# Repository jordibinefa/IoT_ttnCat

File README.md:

# IoT_ttnCat
IoT board designed to be used on ttn.cat workshops

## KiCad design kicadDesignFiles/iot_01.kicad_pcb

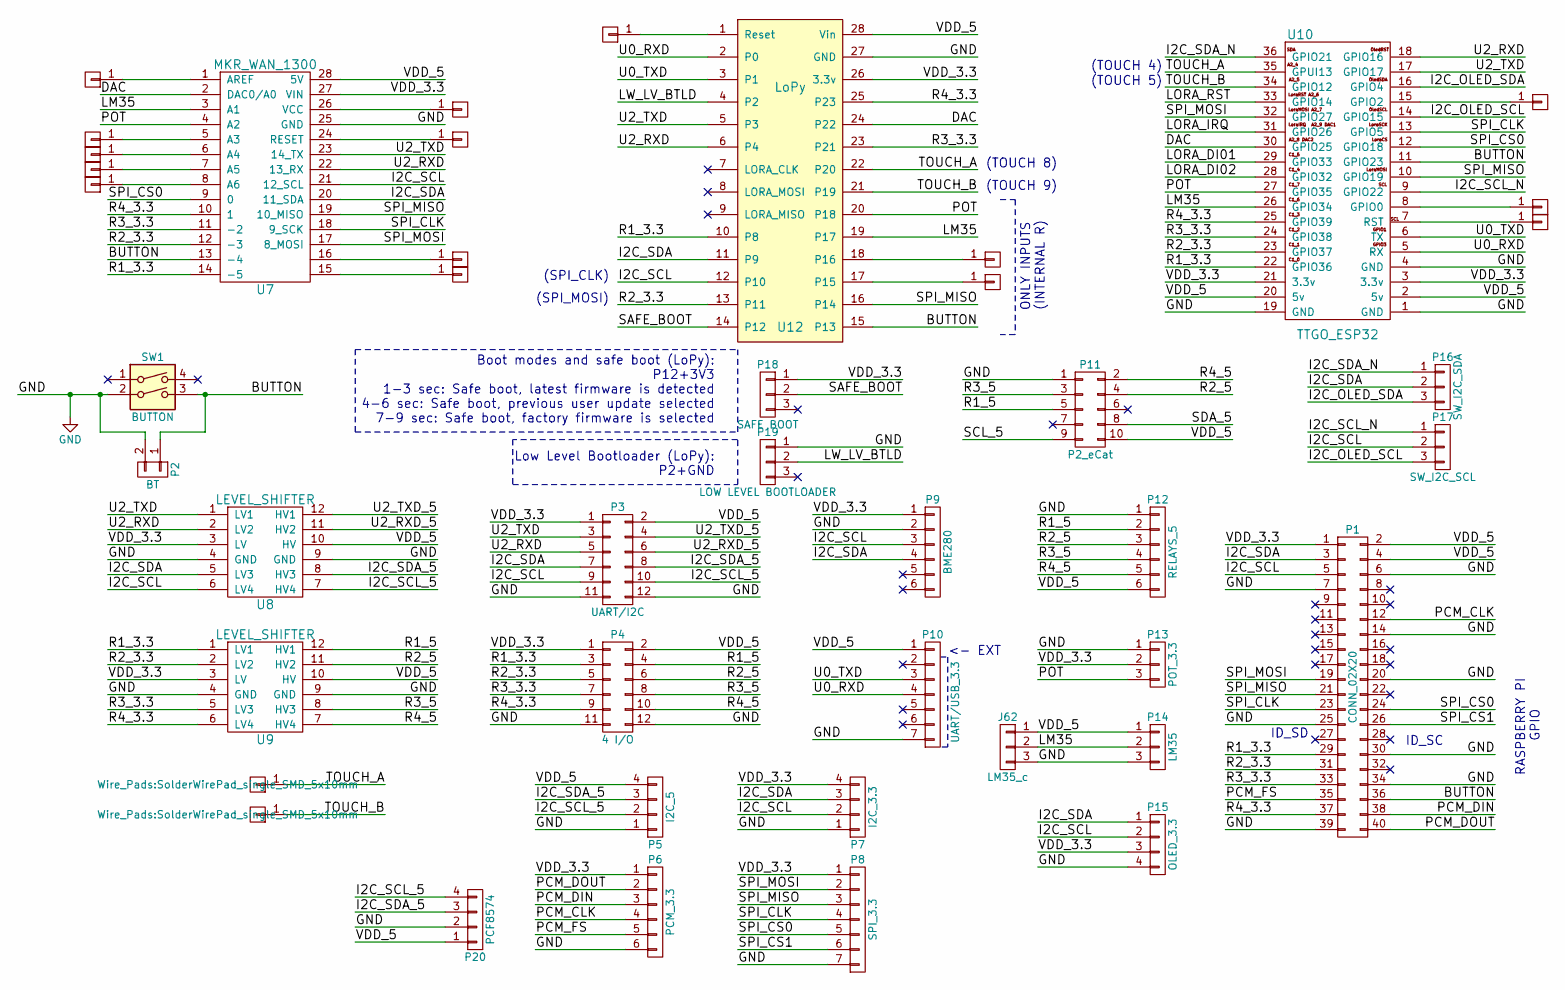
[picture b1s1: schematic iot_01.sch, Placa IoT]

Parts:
J1, J2: Conn_01x01; SolderWirePad_single_SMD_5x10mm
J39, J40, J41, J42, J43, J45, J46, J47, J48, J49, J60, J61, J70, J71, J72: Conn_01x01; Measurement_Point_Square-TH_Small
J62: LM35_c; TO-92_Inline_Wide
P1: CONN_02X20; IDC_Header_Straight_40pins
P2: BT; Pin_Header_Straight_1x02
P3: UART/I2C; Pin_Header_Straight_2x06
P4: 4 I/O; Pin_Header_Straight_2x06
P5: I2C_5; Pin_Header_Straight_1x04
P6: PCM_3.3; Pin_Header_Straight_1x06
P7: I2C_3.3; Pin_Header_Straight_1x04
P8: SPI_3.3; Pin_Header_Straight_1x07
P9: BME280; Pin_Header_Straight_1x06
P10: UART/USB_3.3; Pin_Header_Angled_1x07
P11: P2_eCat; CONN_5_eCAT
P12: RELAYS_5; Pin_Header_Angled_1x06
P13: POT_3.3; Pin_Header_Angled_1x03
P14: LM35; Pin_Header_Straight_1x03
P15: OLED_3.3; Pin_Header_Straight_1x04
P16: SW_I2C_SDA; Pin_Header_Straight_1x03
P17: SW_I2C_SCL; Pin_Header_Straight_1x03
P18: SAFE BOOT; Pin_Header_Straight_1x03
P19: LOW LEVEL BOOTLOADER; Pin_Header_Straight_1x03
P20: PCF8574; Pin_Header_Angled_1x04
SW1: BUTTON; BUTTON_THROUGH_HOLE
U7: MKR_WAN_1300
U8, U9: LEVEL_SHIFTER
U10: TTGO_ESP32
U12: LoPy; LoPy_with_headers

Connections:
/BUTTON: P1.36, P2.1, SW1.3, U7.13 (-4), U10.11 (GPIO23), U12.15 (P13)
/DAC: U7.2 (DAC0/A0), U10.30 (GPIO25), U12.24 (P22)
/I2C_OLED_SCL: P17.3, U10.14 (GPIO15)
/I2C_OLED_SDA: P16.3, U10.16 (GPIO4)
/I2C_SCL: P1.5, P3.9, P7.2, P9.3, P15.2, P17.2, U7.21 (12_SCL), U8.6 (LV4), U12.12 (P10)
/I2C_SCL_5: P3.10, P5.2, P20.4, U8.7 (HV4)
/I2C_SCL_N: P17.1, U10.9 (GPIO22)
/I2C_SDA: P1.3, P3.7, P7.3, P9.4, P15.1, P16.2, U7.20 (11_SDA), U8.5 (LV3), U12.11 (P9)
/I2C_SDA_5: P3.8, P5.3, P20.3, U8.8 (HV3)
/I2C_SDA_N: P16.1, U10.36 (GPIO21)
/LM35: J62.2, P14.2, U7.3 (A1), U10.26 (GPIO34), U12.19 (P17)
/LORA_DI01: U10.29 (GPIO33)
/LORA_DI02: U10.28 (GPIO32)
/LORA_IRQ: U10.31 (GPIO26)
/LORA_RST: U10.33 (GPIO14)
/LW_LV_BTLD: P19.2, U12.4 (P2)
/PCM_CLK: P1.12, P6.4
/PCM_DIN: P1.38, P6.3
/PCM_DOUT: P1.40, P6.2
/PCM_FS: P1.35, P6.5
/POT: P13.3, U7.4 (A2), U10.27 (GPIO35), U12.20 (P18)
/R1_3.3: P1.29, P4.3, U7.14 (-5), U9.1 (LV1), U10.22 (GPIO36), U12.10 (P8)
/R1_5: P4.4, P11.5, P12.2, U9.12 (HV1)
/R2_3.3: P1.31, P4.5, U7.12 (-3), U9.2 (LV2), U10.23 (GPIO37), U12.13 (P11)
/R2_5: P4.6, P11.4, P12.3, U9.11 (HV2)
/R3_3.3: P1.33, P4.7, U7.11 (-2), U9.5 (LV3), U10.24 (GPIO38), U12.23 (P21)
/R3_5: P4.8, P11.3, P12.4, U9.8 (HV3)
/R4_3.3: P1.37, P4.9, U7.10 (1), U9.6 (LV4), U10.25 (GPIO39), U12.25 (P23)
/R4_5: P4.10, P11.2, P12.5, U9.7 (HV4)
/SAFE_BOOT: P18.2, U12.14 (P12)
/SCL_5: P11.9
/SDA_5: P11.8
/SPI_CLK: P1.23, P8.4, U7.18 (9_SCK), U10.13 (GPIO5)
/SPI_CS0: P1.24, P8.5, U7.9 (0), U10.12 (GPIO18)
/SPI_CS1: P1.26, P8.6
/SPI_MISO: P1.21, P8.3, U7.19 (10_MISO), U10.10 (GPIO19), U12.16 (P14)
/SPI_MOSI: P1.19, P8.2, U7.17 (8_MOSI), U10.32 (GPIO27)
/TOUCH_A: J1.1, U10.35 (GPUI13), U12.22 (P20)
/TOUCH_B: J2.1, U10.34 (GPIO12), U12.21 (P19)
/U0_RXD: P10.4, U10.5 (RX), U12.2 (P0)
/U0_TXD: P10.3, U10.6 (TX), U12.3 (P1)
/U2_RXD: P3.5, U7.22 (13_RX), U8.2 (LV2), U10.18 (GPIO16), U12.6 (P4)
/U2_RXD_5: P3.6, U8.11 (HV2)
/U2_TXD: P3.3, U7.23 (14_TX), U8.1 (LV1), U10.17 (GPIO17), U12.5 (P3)
/U2_TXD_5: P3.4, U8.12 (HV1)
/VDD_3.3: P1.1, P3.1, P4.1, P6.1, P7.4, P8.1, P9.1, P13.2, P15.3, P18.1, U7.27 (VIN), U8.3 (LV), U9.3 (LV), U10.3 (3.3v), U10.21 (3.3v), U12.26 (3.3v)
/VDD_5: J62.1, P1.2, P1.4, P3.2, P4.2, P5.4, P10.1, P11.10, P12.6, P14.1, P20.1, U7.28 (5V), U8.10 (HV), U9.10 (HV), U10.2 (5v), U10.20 (5v), U12.28 (Vin)
GND: J62.3, P1.6, P1.7, P1.14, P1.20, P1.25, P1.30, P1.34, P1.39, P2.2, P3.11, P3.12, P4.11, P4.12, P5.1, P6.6, P7.1, P8.7, P9.2, P10.7, P11.1, P12.1, P13.1, P14.3, P15.4, P19.1, P20.2, SW1.2, U7.25 (GND), U8.4 (GND), U8.9 (GND), U9.4 (GND), U9.9 (GND), U10.1 (GND), U10.4 (GND), U10.19 (GND), U12.27 (GND)
unnamed: J39.1, U7.1 (AREF)
unnamed: J40.1, U7.5 (A3)
unnamed: J41.1, U7.6 (A4)
unnamed: J42.1, U7.7 (A5)
unnamed: J43.1, U7.8 (A6)
unnamed: J45.1, U7.26 (VCC)
unnamed: J46.1, U7.24 (RESET)
unnamed: J47.1, U7.16
unnamed: J48.1, U7.15
unnamed: J49.1, U12.1 (Reset)
unnamed: J60.1, U12.18 (P16)
unnamed: J61.1, U12.17 (P15)
unnamed: J70.1, U10.15 (GPIO2)
unnamed: J71.1, U10.8 (GPIO0)
unnamed: J72.1, U10.7 (RST)

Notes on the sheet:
Boot modes and safe boot (LoPy): P12+3V3 1-3 sec: Safe boot, latest firmware is detected 4-6 sec: Safe boot, previous user update selected 7-9 sec: Safe boot, factory firmware is selected
Low Level Bootloader (LoPy): P2+GND
(SPI_CLK)
(TOUCH 4)
(TOUCH 5)
(TOUCH 8)
(TOUCH 9)
(SPI_MOSI)
ONLY INPUTS (INTERNAL R)
RASPBERRY PI GPIO
<- EXT
ID_SC
ID_SD

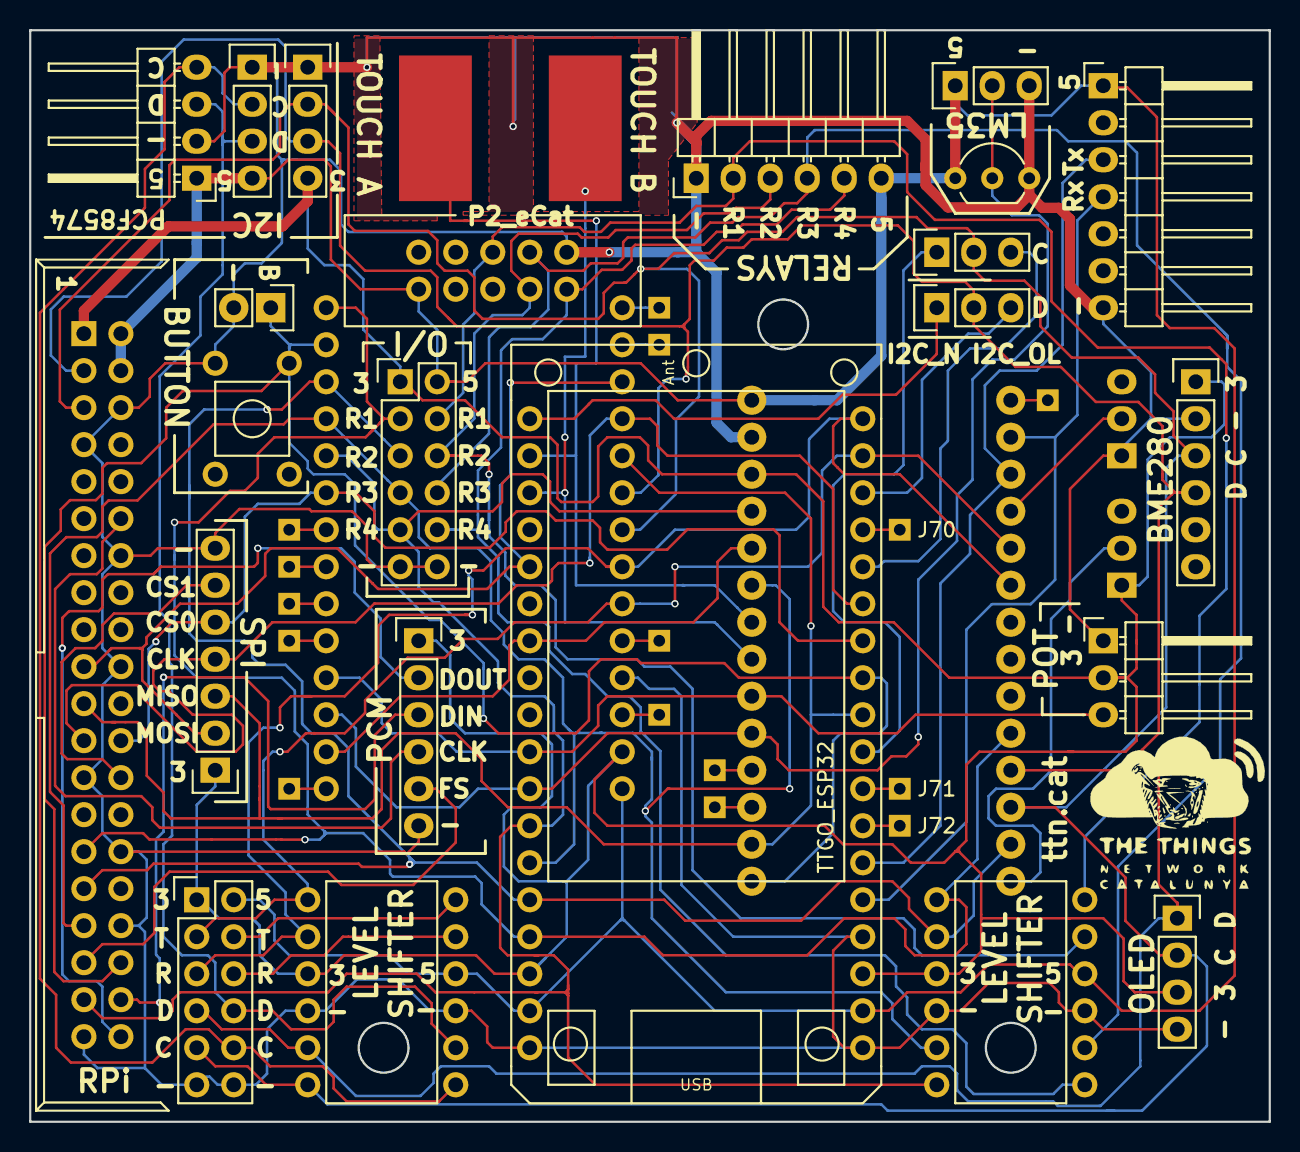
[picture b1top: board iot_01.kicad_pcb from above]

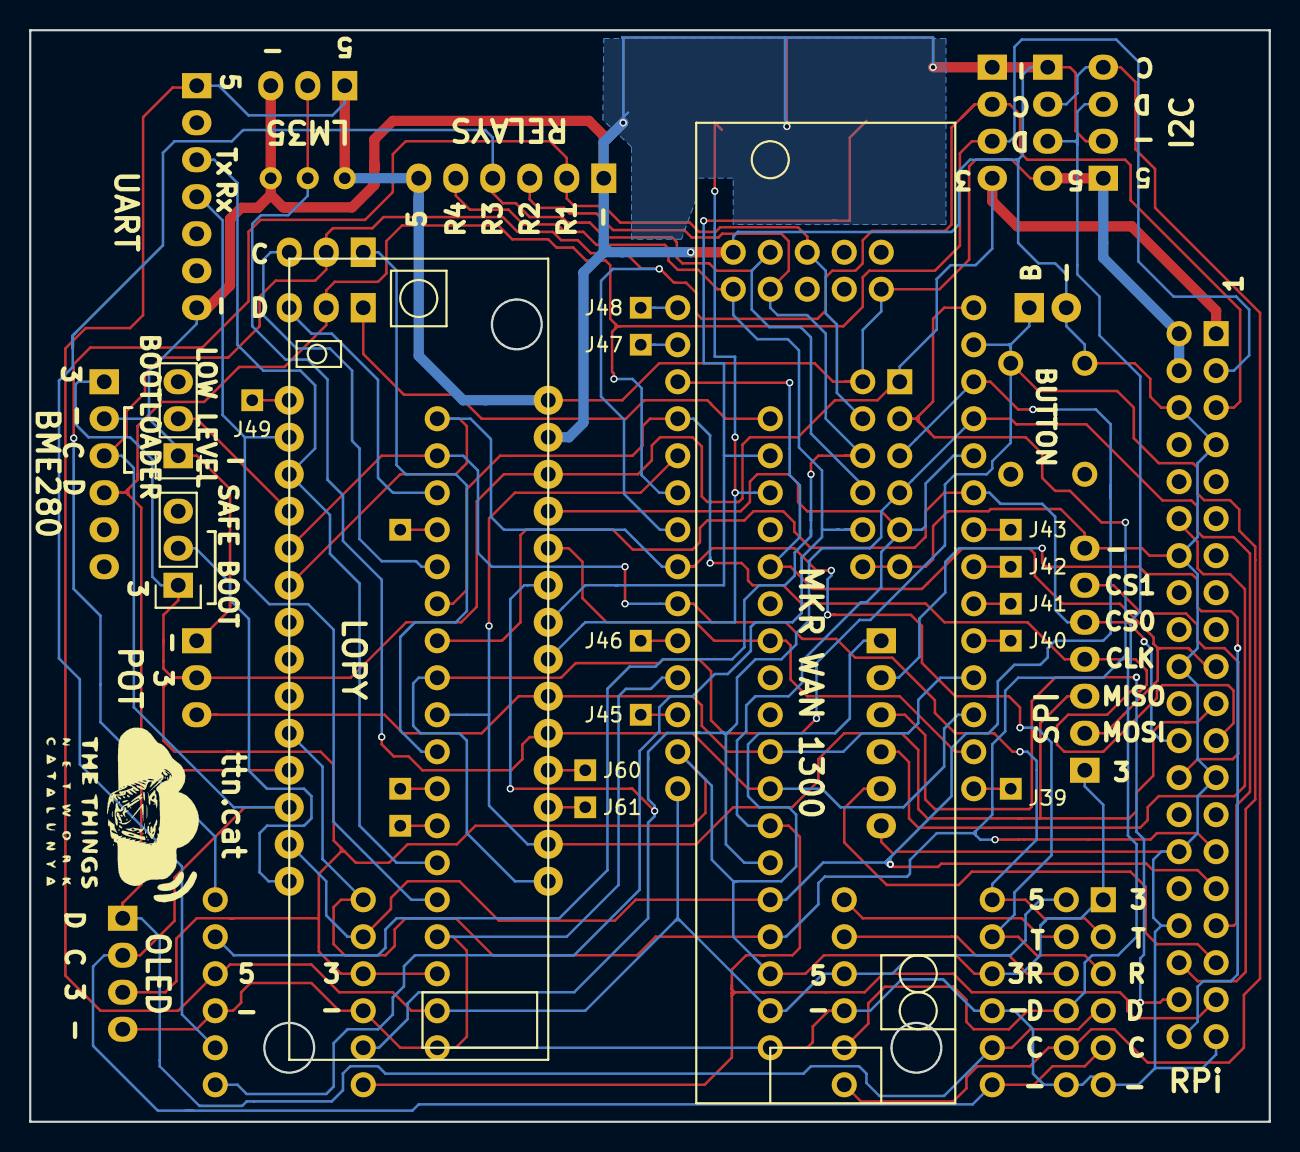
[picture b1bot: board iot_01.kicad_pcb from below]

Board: 2 copper layers, 85.1 x 74.9 mm, 44 parts (16 on the bottom side), 57 nets.
